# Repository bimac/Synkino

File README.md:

# SynkinoLC

Allows sound playback synchronised to a running, jittery Super 8 projector.

SynkinoLC started as a fork of [fwachsmuth/Synkino](https://github.com/fwachsmuth/Synkino) with the following changes:

* While the original Synkino utilized two 8-bit ATmega328P microcontrollers (one for the frontend and one for the backend) SynkinoLC incorporates a single, more powerful 32-bit ARM processor through the use of a Teensy microcontroller board.
* Assembly of SynkinoLC is made simple with only a few off-the-shelf components and no SMD soldering required.
* The firmware has been optimized to fit the 62K flash of the Teensy LC microcontroller board (with some limitations), but Teensy 3.2 is also supported and allows for full functionality.
* Unlike the original Synkino, SynkinoLC is not designed for battery operation. Use any micro-USB phone charger as a power supply unit.
* When connected to a host via USB, SynkinoLC provides direct access to its SD card through MTP (Teensy 3.2 only).
* SD cards can be formatted directly from SynkinoLC as either FAT16, FAT32, or ExFAT (Teensy 3.2 only).
* Storing a track numbered 999 (e.g. "999-24.ogg") to the SD card will cause SynkinoLC to automatically start playing it after startup.

Most parts of [Friedemann's manual for the original Synkino](https://www.filmkorn.org/synkino-instruction-manual/?lang=en) apply for SynkinoLC as well.

## Teensy LC vs Teensy 3.2

When building SynkinoLC, you have the option to use either a Teensy LC or Teensy 3.2 microcontroller board. However, as of the time of writing, Teensy 3.2 microcontrollers are unavailable for purchase due to the current global chip shortage. Although the Teensy LC provides ample processing power for SynkinoLC, it has a few minor limitations related to its smaller flash memory of only 62K (compared to 256K on the Teensy 3.2):

* The binary patch file for the VS1053b audio decoder (```patches.053```) cannot be included with the firmware and needs to be supplied by means of the microSD-card.
* You can store settings for "only" 7 projectors (vs 15 on Teensy 3.2).
* The USB stack has been omitted - you can't use debugging by means of USBSerial. You can, however, use the Teensy's HW serial interface (TX on pin 1, 31250 baud).
* SdFat is running in low-mem mode (no support for exFAT, limited to 32GB cards and 64 character filenames).
* No MTP access to the SD card.
* No option for formatting the SD card.

Neither of these limitations should have a significant impact on the usability of SynkinoLC.

## Building the Firmware

SynkinoLC was created with [PlatformIO](https://docs.platformio.org/en/latest/what-is-platformio.htm) for VSCode. To install PlatformIO:

1. [Download](https://code.visualstudio.com/) and install official Microsoft Visual Studio Code. PlatformIO IDE is built on top of it.
2. Open VSCode Package Manager.
3. Search for the official PlatformIO IDE extension.
4. Install PlatformIO IDE.

See [the official guide](https://docs.platformio.org/en/latest/integration/ide/vscode.html) for more details on the VSCode integration.

To build SynkinoLC:
* open ```Synkino.code-workspace```,
* select the respective project environment (```env:teensyLC``` or ```enc:teensy31```), and
* start the build

The firmware won't fit TeensyLC unless ```SD.h``` is modified as outlined [here](https://github.com/PaulStoffregen/SD/pull/44/commits/c3661d2aef4534b5e9cb3a7f66da09e8c61bf286). A pre-build script will attempt to patch this file automatically.

## Choice of OLED display

SynkinoLC has been designed to work with two types of 1.3" OLED display, based on either SH1106 or SSD1306 driver chips:
* An SH1106 display module (as used in the original Synkino) can be obtained for little money on [aliexpress.com](https://aliexpress.com/wholesale?SearchText=sh1106+128+64) (go for the one that says ```1.30"OLED 4-SPI``` on the back). Other SH1106 modules should work as well, as long as they have identical pin-out (the foot-print for the retaining screws might not be an exact fit though).
* Alternatively, you can go for [Adafruit #938](https://octopart.com/938-adafruit+industries-32979003) which is based on an SSD1306 driver (you'll have to cut two traces on the back of the module to enable SPI as demonstrated [here](https://www.youtube.com/watch?v=SXfV4e_jpf8))

Just connect the display module to the respective slot on the SynkinoLC PCB - the firmware will automatically detect the type of display used.

## Bill of Materials

You'll need the following components to assemble SynkinoLC:

| Qty | Part                                                                                               | Description / Comment                     |
| :-: | :------------------------------------------------------------------------------------------------- | :---------------------------------------- |
|  1  | SynkinoLC PCB                                                                                      |                                           |
|  1  | 1.3" 128x64 monochrome OLED display, SPI                                                           | see separate comments above               |
|  1  | [Teensy-LC](https://octopart.com/dev-13305-sparkfun-66786787)                                      | microcontroller board                     |
|  1  | [Adafruit VS1053 Codec + MicroSD Breakout](https://octopart.com/1381-adafruit+industries-32978404) | audio processing board                    |
|  1  | [Texas Instruments SN74AHC14N](https://octopart.com/sn74ahc14n-texas+instruments-465338)           | inverted Schmitt-trigger                  |
|  2  | [SparkFun ROB-09453](https://octopart.com/rob-09453-sparkfun-67069573)                             | line sensor breakout (analog)             |
|  1  | [Bourns PEC11L-4215F-S0015](https://octopart.com/pec11l-4215f-s0015-bourns-25517430)               | rotary encoder                            |
|  1  | [Cliff CL170842CR](https://octopart.com/cl170842cr-cliff-22810928) (or similar)                    | knob for rotary encoder                   |
|  1  | [TDK PS1240P02BT](https://octopart.com/ps1240p02bt-tdk-8602108)                                    | piezo buzzer                              |
|  2  | [CUI Devices SJ1-2503A](https://octopart.com/sj1-2503a-cui+devices-106235597)                      | 2.5mm audio jack                          |
|  2  | [Tensility CA-2203](https://octopart.com/ca-2203-tensility-19254819)  (or similar)                 | 2.5mm audio cable, stereo                 |
|  2  | [Sullins PPPC071LFBN-RC](https://octopart.com/pppc071lfbn-rc-sullins-271056) (or similar)          | 7 pos female header (for SH1106 display)  |
|  1  | [Sullins PPPC081LFBN-RC](https://octopart.com/pppc081lfbn-rc-sullins-271057) (or similar)          | 8 pos female header (for SSD1306 display) |
|  2  | [Sullins PPPC141LFBN-RC](https://octopart.com/pppc141lfbn-rc-sullins-271063) (or similar)          | 14 pos female header                      |
|  2  | [Sullins PPPC181LFBN-RC](https://octopart.com/pppc181lfbn-rc-sullins-271067) (or similar)          | 18 pos female header                      |
|  1  | [Adam Tech PH1-07-UA](https://octopart.com/ph1-07-ua-adam+tech-7873139) (or similar)               | 7 pos male header (for SH1106 display)    |
|  1  | [Adam Tech PH1-08-UA](https://octopart.com/ph1-08-ua-adam+tech-13205589) (or similar)              | 8 pos male header (for SSD1306 display)   |
|  2  | [Adam Tech PH1-14-UA](https://octopart.com/ph1-14-ua-adam+tech-14467007) (or similar)              | 14 pos male header                        |

Click [here](https://octopart.com/bom-tool/omFmd0tC) for a full BOM on [octopart.com](https://octopart.com) (with SSD1306 display and not including the PCB). All necessary components should be obtainable for about USD/EUR 80-100 including shipping - depending on your choice of display and PCB service.

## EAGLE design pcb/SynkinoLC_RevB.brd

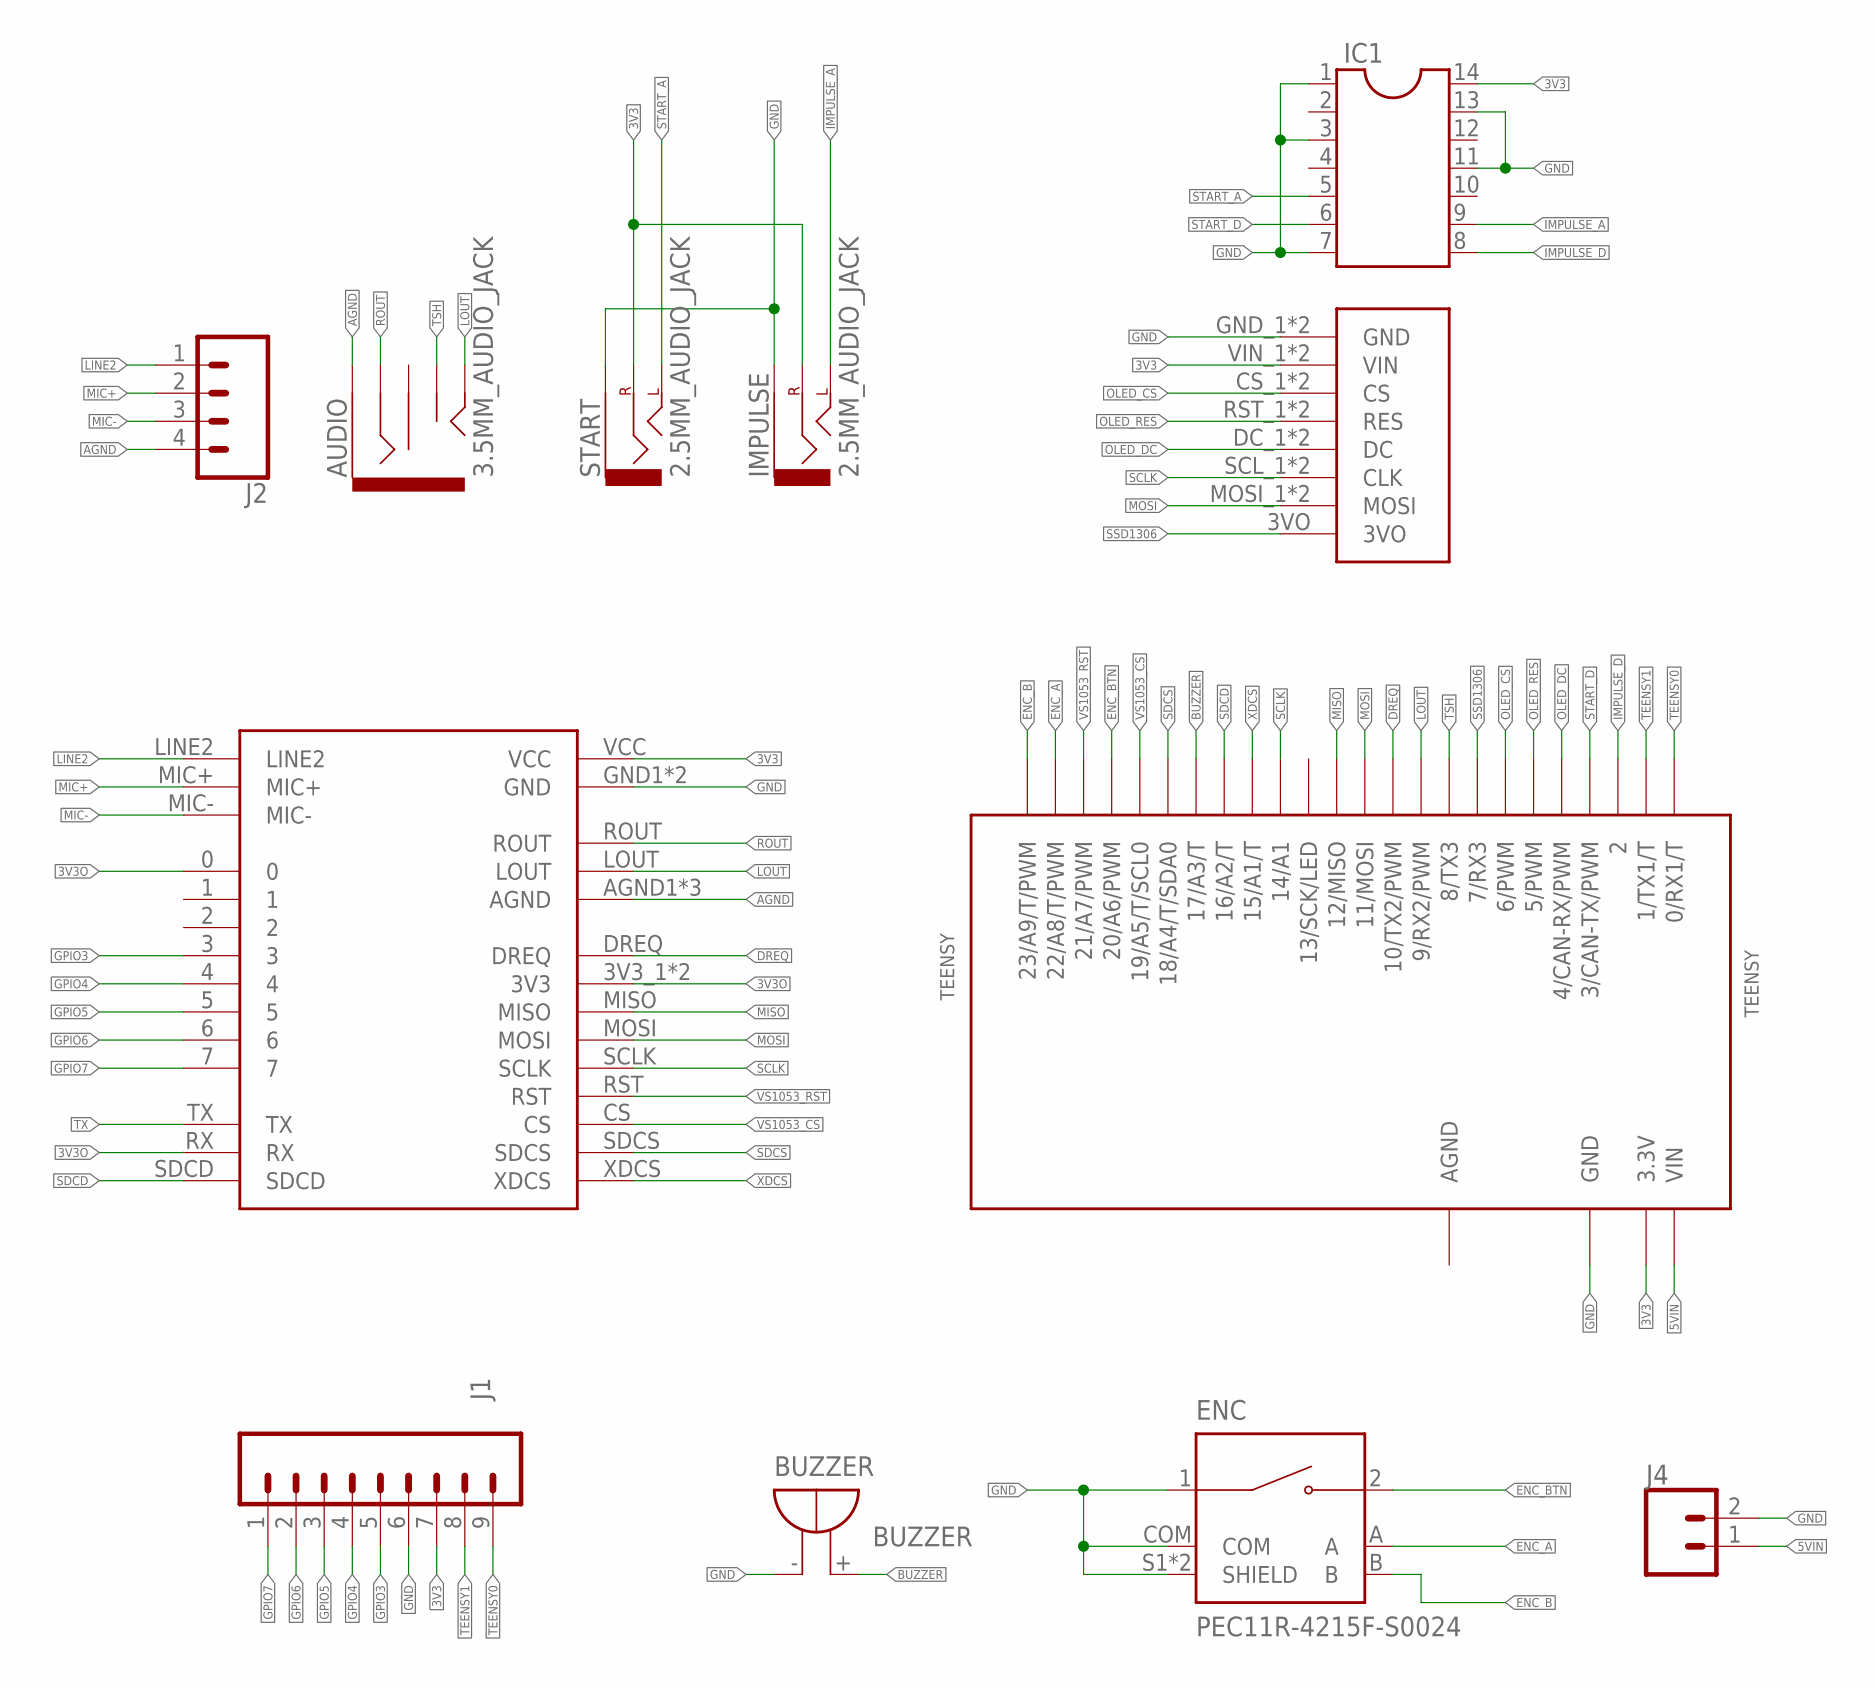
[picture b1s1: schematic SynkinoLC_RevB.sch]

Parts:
AUDIO: 3.5MM_AUDIO_JACK
BUZZER: BUZZER
DISPLAY: SPI_DISPLAYSPI_DISPLAY2; SPI_DISPLAY2
ENC: PEC11R-4215F-S0024; XDCR_PEC11R-4215F-S0024
IC1: DIL14R; DIL14_ROUND
IMPULSE: 2.5MM_AUDIO_JACK
J1: CONN_09NO_SILK; 1X09_NO_SILK
J2: CONN_04; 1X04
J4: CONN_021X02_NO_SILK; 1X02_NO_SILK
START: 2.5MM_AUDIO_JACK
TEENSY: TEENSY
U$2: VS1053B

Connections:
3V3: DISPLAY.VIN_1 (VIN), DISPLAY.VIN_2 (VIN), IC1.14, IMPULSE.RING (RIGHT), J1.7, START.RING (RIGHT), TEENSY.3.3V, U$2.VCC
3V3O: U$2.0, U$2.3V3_1 (3V3), U$2.3V3_2 (3V3), U$2.RX
5VIN: J4.1, TEENSY.VIN
AGND: AUDIO.SLEEVE, J2.4, TEENSY.AGND, U$2.AGND1 (AGND), U$2.AGND2 (AGND), U$2.AGND3 (AGND)
BUZZER: BUZZER.+ (-), TEENSY.17/A3 (17/A3/T)
DREQ: TEENSY.10 (10/TX2/PWM), U$2.DREQ
ENC_A: ENC.A, TEENSY.22/A8 (22/A8/T/PWM)
ENC_B: ENC.B, TEENSY.23/A9 (23/A9/T/PWM)
ENC_BTN: ENC.2, TEENSY.20/A6 (20/A6/PWM)
GND: BUZZER.- (+), DISPLAY.GND_1 (GND), DISPLAY.GND_2 (GND), ENC.1, ENC.COM, ENC.S1 (SHIELD), ENC.S2 (SHIELD), IC1.1, IC1.3, IC1.7, IC1.11, IC1.13, IMPULSE.SLEEVE, J1.6, J4.2, START.SLEEVE, TEENSY.GND, U$2.GND1 (GND), U$2.GND2 (GND)
GPIO3: J1.5, U$2.3
GPIO4: J1.4, U$2.4
GPIO5: J1.3, U$2.5
GPIO6: J1.2, U$2.6
GPIO7: J1.1, U$2.7
IMPULSE_A: IC1.9, IMPULSE.TIP_1 (LEFT), IMPULSE.TIP_2 (LEFT)
IMPULSE_D: IC1.8, TEENSY.2
LINE2: J2.1, U$2.LINE2
LOUT: AUDIO.TIP, TEENSY.9 (9/RX2/PWM), U$2.LOUT
MIC+: J2.2, U$2.MIC+
MIC-: J2.3, U$2.MIC-
MISO: TEENSY.12 (12/MISO), U$2.MISO
MOSI: DISPLAY.MOSI_1 (MOSI), DISPLAY.MOSI_2 (MOSI), TEENSY.11 (11/MOSI), U$2.MOSI
OLED_CS: DISPLAY.CS_1 (CS), DISPLAY.CS_2 (CS), TEENSY.6 (6/PWM)
OLED_DC: DISPLAY.DC_1 (DC), DISPLAY.DC_2 (DC), TEENSY.4 (4/CAN-RX/PWM)
OLED_RES: DISPLAY.RST_1 (RES), DISPLAY.RST_2 (RES), TEENSY.5 (5/PWM)
ROUT: AUDIO.RING, U$2.ROUT
SCLK: DISPLAY.SCL_1 (CLK), DISPLAY.SCL_2 (CLK), TEENSY.14/A0 (14/A1), U$2.SCLK
SDCD: TEENSY.16/A2 (16/A2/T), U$2.SDCD
SDCS: TEENSY.18/A4 (18/A4/T/SDA0), U$2.SDCS
SSD1306: DISPLAY.3VO, TEENSY.7 (7/RX3)
START_A: IC1.5, START.TIP_1 (LEFT), START.TIP_2 (LEFT)
START_D: IC1.6, TEENSY.3 (3/CAN-TX/PWM)
TEENSY0: J1.9, TEENSY.0 (0/RX1/T)
TEENSY1: J1.8, TEENSY.1 (1/TX1/T)
TSH: AUDIO.TSH, TEENSY.8 (8/TX3)
TX: U$2.TX
VS1053_CS: TEENSY.19/A5 (19/A5/T/SCL0), U$2.CS
VS1053_RST: TEENSY.21/A7 (21/A7/PWM), U$2.RST
XDCS: TEENSY.15/A1 (15/A1/T), U$2.XDCS

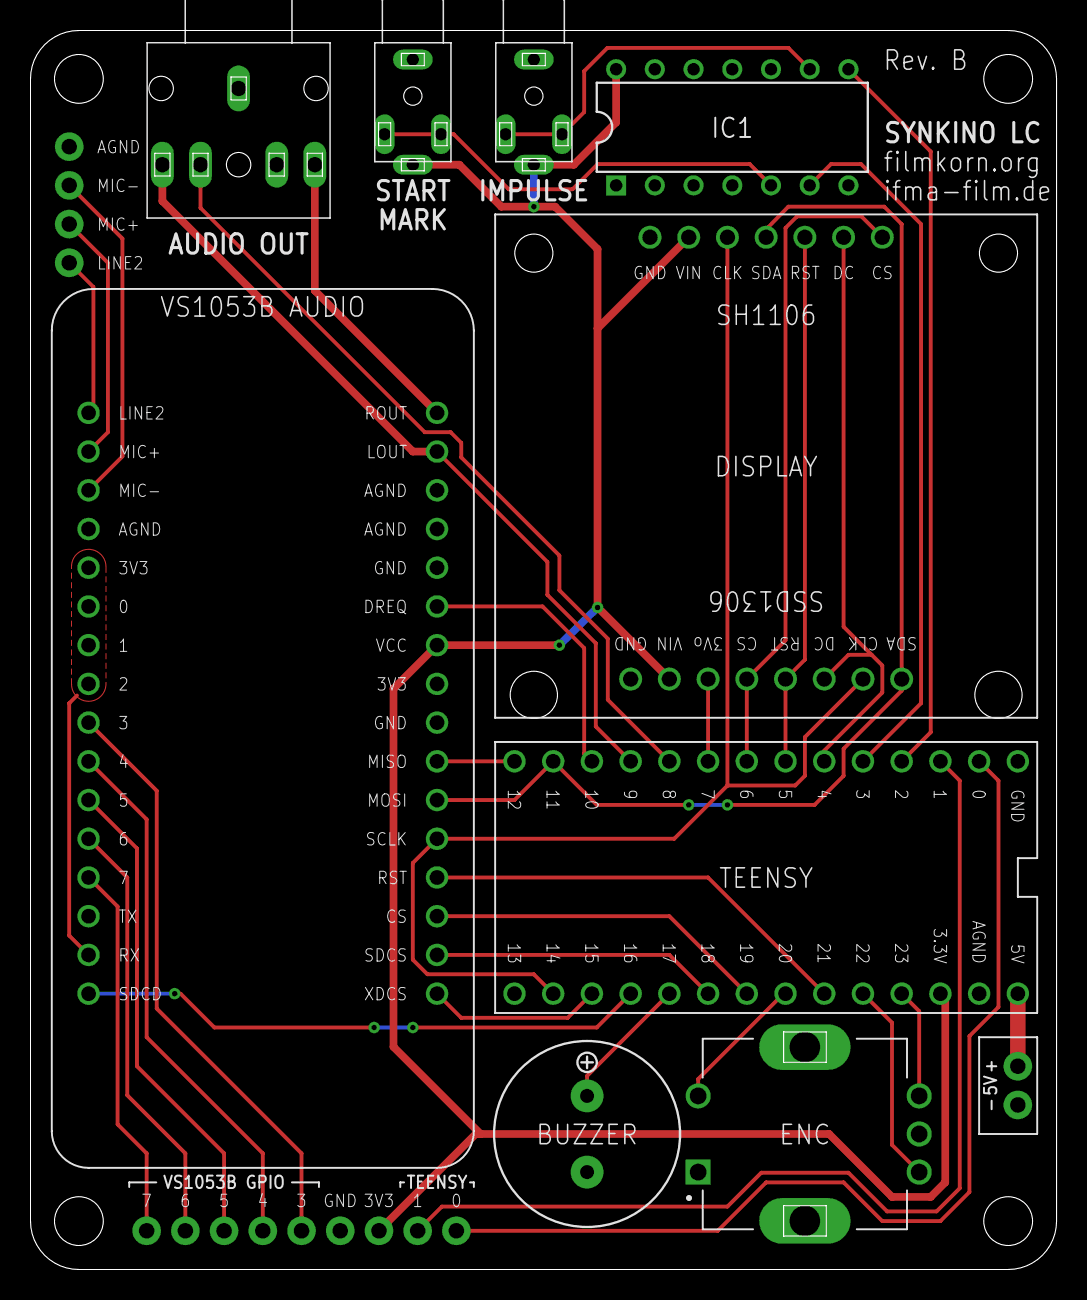
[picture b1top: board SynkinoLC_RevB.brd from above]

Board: 2 copper layers, 67.3 x 81.3 mm, 12 parts (0 on the bottom side), 39 nets.

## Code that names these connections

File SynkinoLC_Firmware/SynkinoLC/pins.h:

#pragma once

#define SPI_MOSI       11
#define SPI_MISO       12
#define SPI_SCK        14  // Alternative pin to bypass the LED

#define OLED_DC         4
#define OLED_CS         6
#define OLED_RST        5
#define OLED_DET        7

#define RSH             8
#define TSH             9

#define VS1053_RST     21  // reset pin
#define VS1053_CS      19  // chip select pin
#define VS1053_DCS     15  // data/command select
#define VS1053_DREQ    10  // data request
#define VS1053_SDCS    18  // SD card chip select
#define VS1053_SDCD    16  // SD card detection

#define ENC_A          23
#define ENC_B          22
#define ENC_BTN        20

#define PIN_BUZZER     17

#define IMPULSE         2
#define STARTMARK       3

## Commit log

2022-06-18 Hello world!
2022-06-18 Adding the encoder
2022-06-18 initial work on menu
2022-06-19 projector menu
2022-06-19 add VS1053B patch 2.9
2022-06-20 add patch routine
2022-06-22 Add buzzer
2022-07-01 store patches.053 in flash
2022-07-06 add teensyLC as build target / adapt patch routine
2022-07-06 fancy new booth splash
2022-07-06 buzzer freqs as macros
2022-07-07 Update SynkinoLC.ino
    Add prompt for projector deletion
2022-07-07 Trying to simplify things
2022-07-07 Trying to simplify things #2
2022-07-08 detect presence of SD card
2022-07-09 simplify e2reader
2022-07-11 pin definitions for first production run
2022-07-11 auto-detect display type / test impulse feature
2022-07-12 add buzzer class
2022-07-13 add VS1053B class
2022-07-13 update buzzer class
2022-07-22 mostly work on the front-end
2022-07-25 various updates
    - projector object should be mostly finished
    - new ui object
2022-07-26 various updates II
2022-07-28 various updates III
2022-07-28 menu: avoid nested switch statements
2022-08-01 various updates IV
2022-08-01 PCB layouts for Revisions A and B
2022-08-04 various updates V
    - HW serial debugging on TeensyLC
    - work on the PID
    - pin definitions for HW Rev B
2022-08-07 cleaning up
2022-08-09 grab bag
    - got rid of all instances of printf()
    - work on the playback UI
    - clean-up
2022-08-09 more clean-up
2022-08-09 wrapping things up for the first alpha
2022-08-10 fix startmark-offset
2022-08-17 conversion from .ino to .cpp
2022-08-17 reorganize directory structure
2022-08-17 remove teensy40 build environment
2022-09-23 add non-blocking melody() function
2022-10-01 add offset correction and manual start
2022-10-05 busy bee better buzz
2022-10-25 reset more vars before running PID
2022-10-25 cleaning up some more
2022-10-25 add patch routine for SD.h
2022-10-25 stick to old version of Adafruit VS1053 Library (smaller)
2022-10-25 patch routine currently doesn't work on windows
2022-10-25 more size optimization for teensyLC
2022-10-25 make patch routine for SD.h work cross-platform
2022-10-25 clean up pcb folder
2022-11-04 add detection/UI for loop film
2022-11-21 experimental support for MTP
2022-11-21 increment version number
2022-11-22 some changes to the MTP code
2022-11-28 Looping half working
2022-11-28 second commit
2022-12-01 implement autostart feature
2022-12-01 correction for MTP patching routing
2022-12-01 Loop working, solved the delay at the beginning of each iteration by modifying the speedControlPid() funciton, the original lines are commented out.
    q
2022-12-14 Working
2022-12-15 Borrando .pio, poniéndolo en el gitignore
2023-01-17 fix autostart
2023-01-17 autostart feature (#2)
    a track numbered 999 will automatically begin playing after start-up
2023-01-17 more size optimizations for TeensyLC and minor corrections
2023-01-17 pull in latest changes from main branch (#3)
    * autostart feature (#2)
    a track numbered 999 will automatically begin playing after start-up
    * Update README.md
    * more size optimizations for TeensyLC and minor corrections
2023-01-17 some clean-up
2023-01-17 some more clean-up
2023-01-31 remove readWRAM()
2023-01-31 add methods for determining state of buffers
2023-01-31 enable 15/16 resampler only when necessary
2023-01-31 drive LED low at end of impulse test
2023-01-31 add more macro definitions of registers
2023-01-31 correct PID output limits
2023-01-31 various small corrections
2023-01-31 clean-up: macros
2023-01-31 added a few methods for handling OGG files
2023-02-02 simplify reading/writing to WRAM
2023-02-02 implement getAudioMillis()
2023-02-02 Simplify handling of VS1053B patches
2023-02-02 correction for average() method
2023-02-04 add option for formatting the SD card
2023-02-04 make sure that buzzer is silenced after an impulse test

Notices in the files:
parts and their libraries:
SparkFun-Connectors: Licensing: Creative Commons ShareAlike 4.0 International - https://creativecommons.org/licenses/by-sa/4.0
